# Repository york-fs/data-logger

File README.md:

# Data Logging Board

This is a custom PCB data-logger designed to work on our Formula Student car. It captures data from the vehicle's CAN bus, transmits telemetry, and logs to an SD card. Additionally, the data logger stores configuration information on EEPROM. 

## Key Features
- **CAN bus interface** for vehicle data logging  
- **SD card slot** for onboard storage
- **EEPROM** for storing config data
- **Real-time clock (RTC)** with battery backup for accurate timestamps  
- **USB interface** for configuration and file transfer  
- **UART output** to a SiK telemetry radio for live data streaming  
- **Status LEDs** for logging, USB power, and telemetry status

## PCB Notes
- Designed in KiCad 9.0
- 3D models stored in external library (lib)

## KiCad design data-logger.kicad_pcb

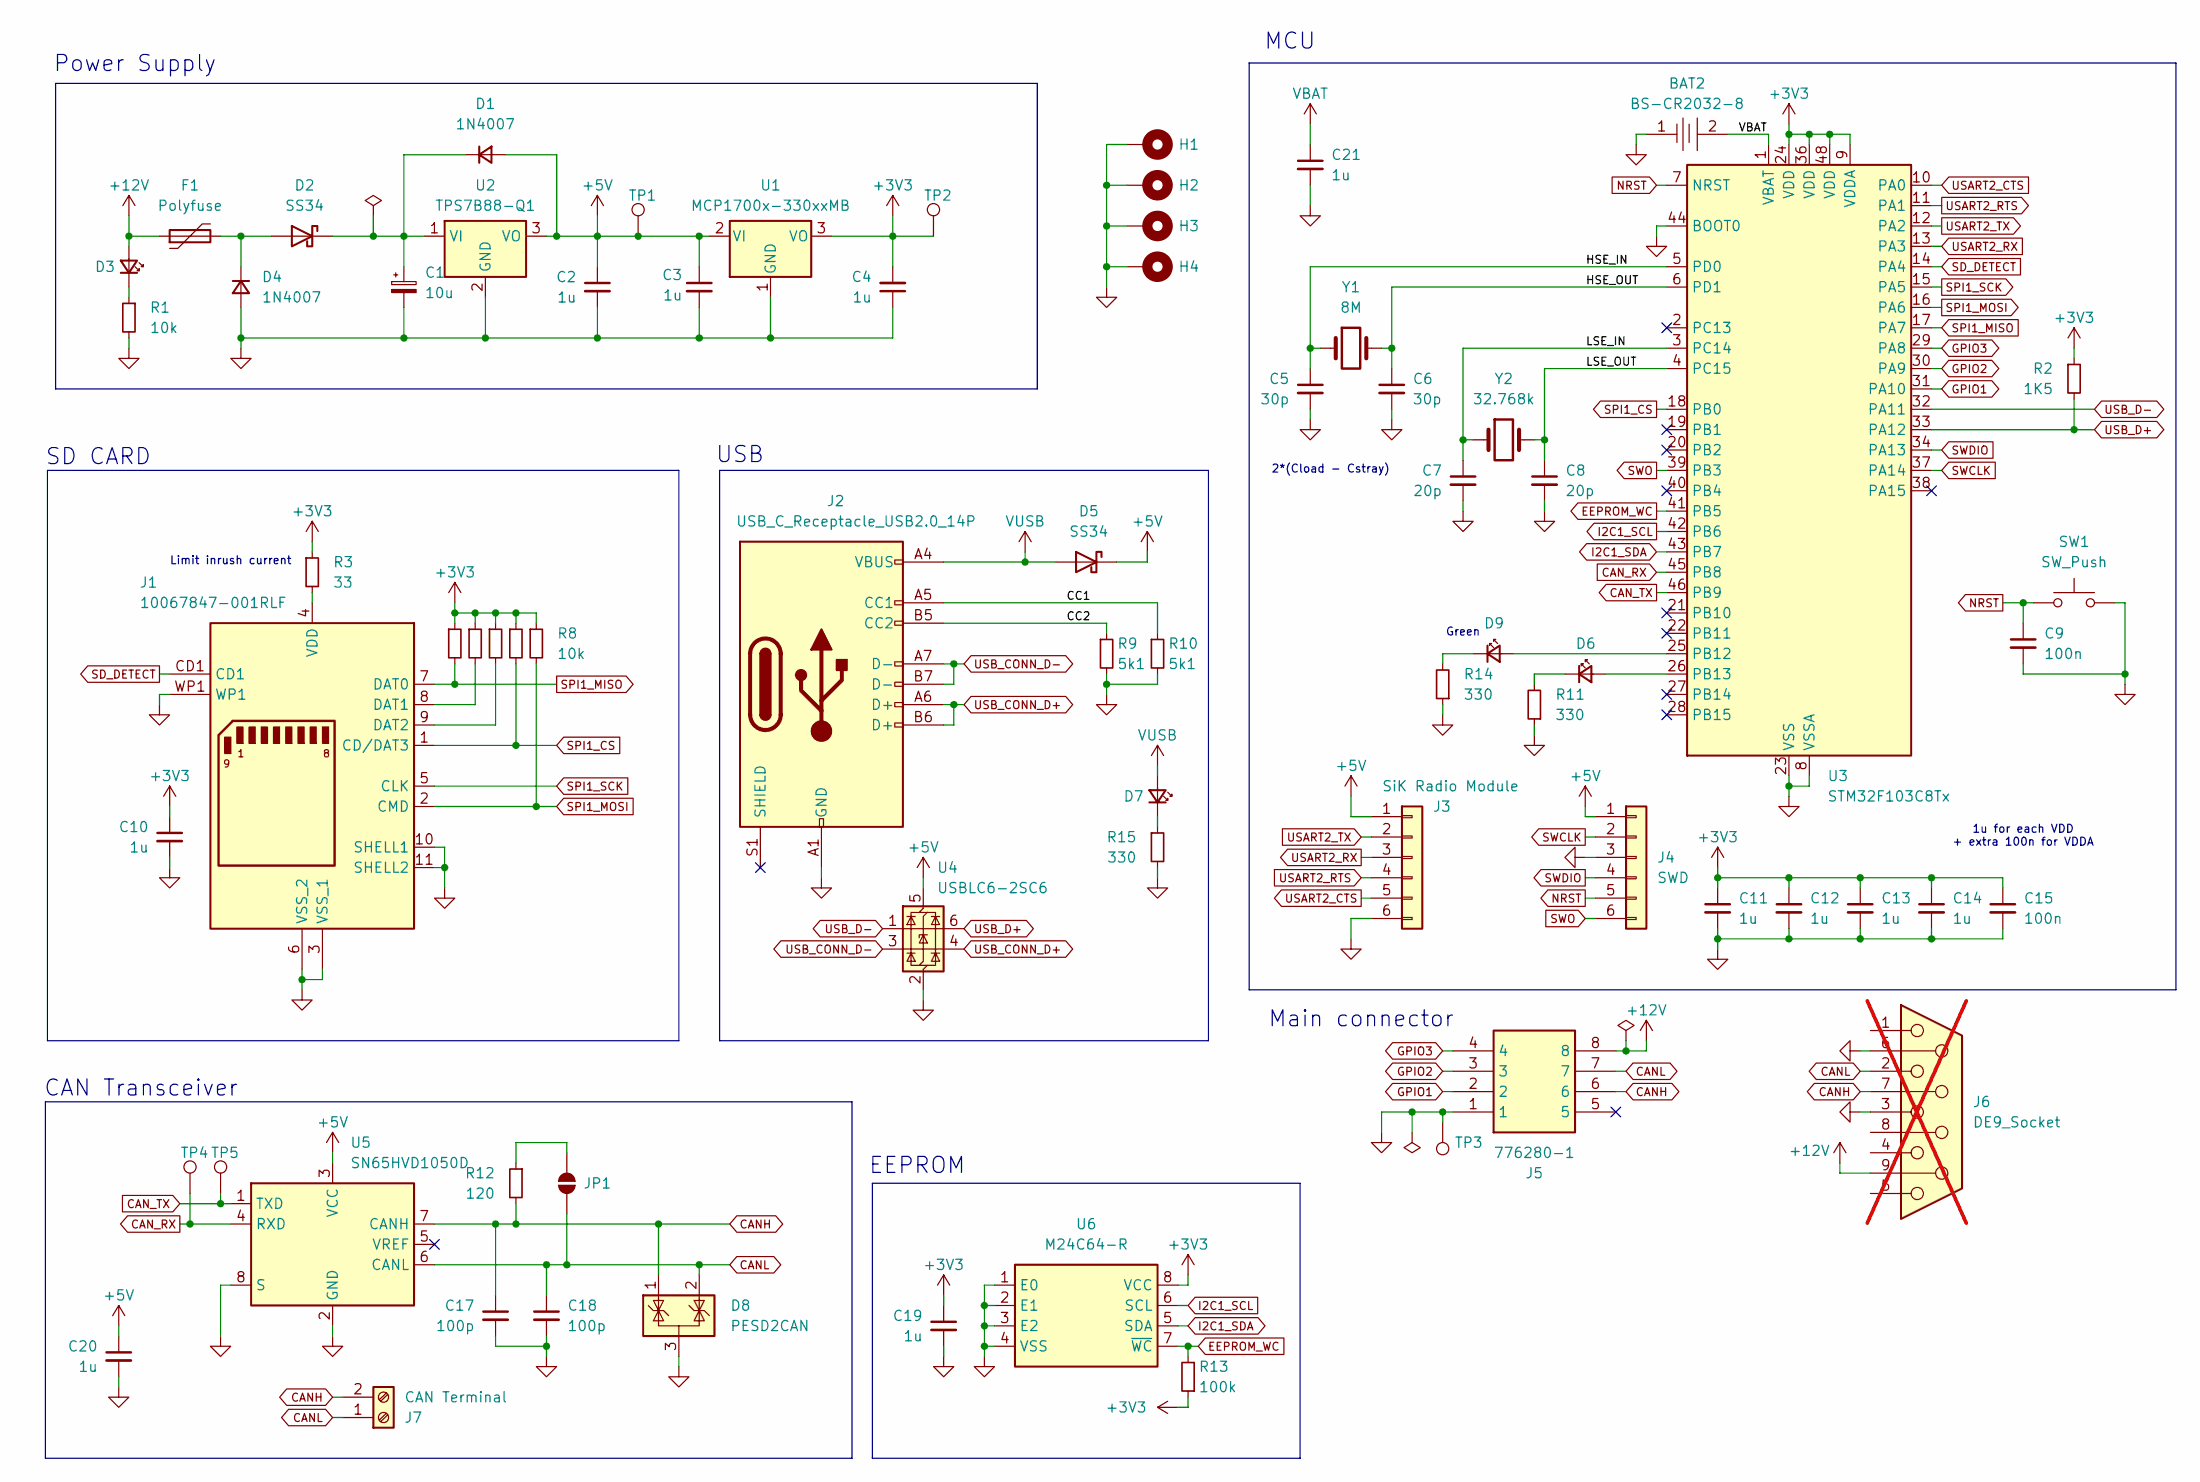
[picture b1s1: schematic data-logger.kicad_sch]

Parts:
BAT2: BS-CR2032-8; BAT-SMD_BS-CR2032-8; LCSC Part C7498149
C1: 10u; CP_Elec_6.3x5.4
C2, C3, C4, C10, C11, C12, C13, C14, C19, C20, C21: 1u; C_0603_1608Metric
C5, C6: 30p; C_0603_1608Metric
C7, C8: 20p; C_0603_1608Metric
C9, C15: 100n; C_0603_1608Metric
C17, C18: 100p; C_0603_1608Metric
D1, D4: 1N4007; D_SOD-123F
D2, D5: SS34; D_SMA
D3, D6, D7, D9: LED_Small; LED_0603_1608Metric
D8: PESD2CAN; SOT-23
F1: Polyfuse; R_0805_2012Metric
H1, H2, H3, H4: MountingHole_Pad; MountingHole_3.2mm_M3_Pad_Via
J1: 10067847-001RLF; 10067847-001RLF_AMP; Mouser Part Number 649-10067847-001RLF
J2: USB_C_Receptacle_USB2.0_14P; USB_C_Receptacle_G-Switch_GT-USB-7010ASV
J3: SiK Radio Module; JST_PH_B6B-PH-K_1x06_P2.00mm_Vertical
J4: SWD; PinHeader_1x06_P2.54mm_Vertical
J5: 776280-1; Mouser Part Number 571-776280-1
J6: DE9_Socket; not fitted
J7: CAN Terminal; TerminalBlock_bornier-2_P5.08mm
JP1: SolderJumper_2_Open; SolderJumper-2_P1.3mm_Open_RoundedPad1.0x1.5mm
R1, R8: 10k; R_0603_1608Metric
R2: 1K5; R_0603_1608Metric
R3, R4, R5, R6, R7: 33; R_0603_1608Metric
R9, R10: 5k1; R_0603_1608Metric
R11, R14, R15: 330; R_0603_1608Metric
R12: 120; R_0603_1608Metric
R13: 100k; R_0603_1608Metric
SW1: SW_Push; SW_Push_SPST_NO_Alps_SKRK
TP1, TP2, TP3, TP4, TP5: TestPoint; TestPoint_Keystone_5000-5004_Miniature
U1: MCP1700x-330xxMB; SOT-89-3
U2: TPS7B88-Q1; TO-252-2
U3: STM32F103C8Tx; LQFP-48_7x7mm_P0.5mm
U4: USBLC6-2SC6; SOT-23-6
U5: SN65HVD1050D; SOIC-8_3.9x4.9mm_P1.27mm
U6: M24C64-R; SOIC-8_3.9x4.9mm_P1.27mm
Y1: 8M; Crystal_SMD_5032-2Pin_5.0x3.2mm
Y2: 32.768k; Crystal_SMD_G8-2Pin_3.2x1.5mm

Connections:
+3V3: C4.2, C10.1, C11.1, C12.1, C13.1, C14.1, C15.1, C19.1, R2.1, R3.1, R4.1, R5.1, R6.1, R7.1, R8.1, R13.1, TP2.1, U1.3 (VO), U3.9 (VDDA), U3.24 (VDD), U3.36 (VDD), U3.48 (VDD), U6.8 (VCC)
+5V: C2.1, C3.1, C20.1, D1.2 (A), D5.1 (K), J3.1, J4.1, TP1.1, U1.2 (VI), U2.3 (VO), U4.5 (VBUS), U5.3 (VCC)
+12V: D3.2 (A), F1.1, J5.8, J6.9
/CC1: J2.A5 (CC1), R10.1
/CC2: J2.B5 (CC2), R9.1
/HSE_IN: C5.1, U3.5 (PD0), Y1.1
/HSE_OUT: C6.1, U3.6 (PD1), Y1.2
/LSE_IN: C7.1, U3.3 (PC14), Y2.1
/LSE_OUT: C8.1, U3.4 (PC15), Y2.2
CANH: C17.1, D8.1 (K), J5.6, J6.7, J7.2, R12.2, U5.7 (CANH)
CANL: C18.1, D8.2 (K), J5.7, J6.2, J7.1, JP1.2 (B), U5.6 (CANL)
CAN_RX: TP4.1, U3.45 (PB8), U5.4 (RXD)
CAN_TX: TP5.1, U3.46 (PB9), U5.1 (TXD)
EEPROM_WC: R13.2, U3.41 (PB5), U6.7 (~WC)
GND: BAT2.1, C1.2, C2.2, C3.2, C4.1, C5.2, C6.2, C7.2, C8.2, C9.2, C10.2, C11.2, C12.2, C13.2, C14.2, C15.2, C17.2, C18.2, C19.2, C20.2, C21.2, D4.2 (A), D8.3 (A), H1.1, H2.1, H3.1, H4.1, J1.3 (VSS_1), J1.6 (VSS_2), J1.10 (SHELL1), J1.11 (SHELL2), J1.WP1, J2.A1 (GND), J2.A12 (GND), J2.B1 (GND), J2.B12 (GND), J3.6, J4.3, J5.1, J6.3, J6.6, R1.2, R9.2, R10.2, R11.1, R14.1, R15.2, SW1.2, TP3.1, U1.1 (GND), U2.2 (GND), U3.8 (VSSA), U3.23 (VSS), U3.35 (VSS), U3.44 (BOOT0), U3.47 (VSS), U4.2 (GND), U5.2 (GND), U5.8 (S), U6.1 (E0), U6.2 (E1), U6.3 (E2), U6.4 (VSS)
GPIO1: J5.2, U3.31 (PA10)
GPIO2: J5.3, U3.30 (PA9)
GPIO3: J5.4, U3.29 (PA8)
I2C1_SCL: U3.42 (PB6), U6.6 (SCL)
I2C1_SDA: U3.43 (PB7), U6.5 (SDA)
NRST: C9.1, J4.5, SW1.1, U3.7 (NRST)
unnamed: C1.1, D1.1 (K), D2.1 (K), U2.1 (VI)
unnamed: D2.2 (A), D4.1 (K), F1.2
unnamed: D3.1 (K), R1.1
unnamed: D6.2 (A), U3.26 (PB13)
unnamed: D6.1 (K), R11.2
unnamed: D7.1 (K), R15.1
unnamed: D9.2 (A), U3.25 (PB12)
unnamed: D9.1 (K), R14.2
unnamed: J1.8 (DAT1), R5.2
unnamed: J1.9 (DAT2), R6.2
unnamed: J1.4 (VDD), R3.2
unnamed: JP1.1 (A), R12.1
SD_DETECT: J1.CD1, U3.14 (PA4)
SPI1_CS: J1.1 (CD/DAT3), R7.2, U3.18 (PB0)
SPI1_MISO: J1.7 (DAT0), R4.2, U3.17 (PA7)
SPI1_MOSI: J1.2 (CMD), R8.2, U3.16 (PA6)
SPI1_SCK: J1.5 (CLK), U3.15 (PA5)
SWCLK: J4.2, U3.37 (PA14)
SWDIO: J4.4, U3.34 (PA13)
SWO: J4.6, U3.39 (PB3)
USART2_CTS: J3.5, U3.10 (PA0)
USART2_RTS: J3.4, U3.11 (PA1)
USART2_RX: J3.3, U3.13 (PA3)
USART2_TX: J3.2, U3.12 (PA2)
USB_CONN_D+: J2.A6 (D+), J2.B6 (D+), U4.4 (I/O2)
USB_CONN_D-: J2.A7 (D-), J2.B7 (D-), U4.3 (I/O2)
USB_D+: R2.2, U3.33 (PA12), U4.6 (I/O1)
USB_D-: U3.32 (PA11), U4.1 (I/O1)
VBAT: BAT2.2, C21.1, U3.1 (VBAT)
VUSB: D5.2 (A), D7.2 (A), J2.A4 (VBUS), J2.A9 (VBUS), J2.B4 (VBUS), J2.B9 (VBUS)

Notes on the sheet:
SD CARD
Main connector
1u for each VDD + extra 100n for VDDA
CAN Transceiver
2*(Cload - Cstray)
MCU
USB
EEPROM
Limit inrush current
Green
Power Supply

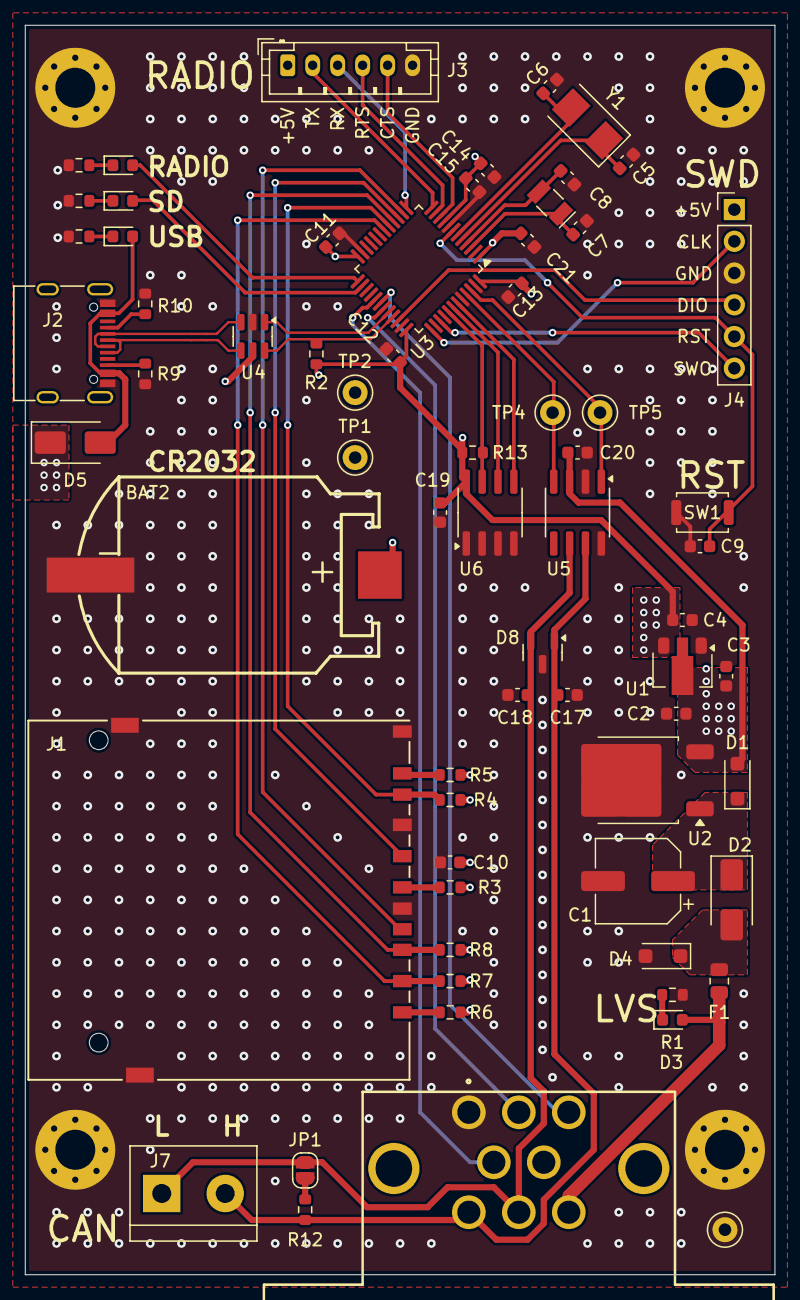
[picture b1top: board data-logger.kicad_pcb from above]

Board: 4 copper layers, 60.0 x 100.0 mm, 71 parts (0 on the bottom side), 51 nets.

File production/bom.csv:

Designator,Footprint,Quantity,Value,LCSC Part #
BAT2,BAT-SMD_BS-CR2032-8,1,BS-CR2032-8,C7498149
C1,CP_Elec_6.3x5.4,1,10u,
"C10, C11, C12, C13, C14, C19, C2, C20, C21, C3, C4",0603,11,1u,
"C15, C9",0603,2,100n,
"C17, C18",0603,2,100p,
"C5, C6",0603,2,30p,
"C7, C8",0603,2,20p,
"D1, D4",D_SOD-123F,2,1N4007,
"D2, D5",D_SMA,2,SS34,
"D3, D6, D7, D9",0603,4,LED_Small,
D8,SOT-23,1,PESD2CAN,
F1,0805,1,Polyfuse,
"H1, H2, H3, H4",MountingHole_3.2mm_M3_Pad_Via,4,MountingHole_Pad,
J1,10067847-001RLF_AMP,1,10067847-001RLF,
J2,USB_C_Receptacle_G-Switch_GT-USB-7010ASV,1,USB_C_Receptacle_USB2.0_14P,
J3,JST_PH_B6B-PH-K_1x06_P2.00mm_Vertical,1,SiK Radio Module,
J4,PinHeader_1x06_P2.54mm_Vertical,1,SWD,
J5,776280-1,1,776280-1,
J7,TerminalBlock_bornier-2_P5.08mm,1,CAN Terminal,
"R1, R8",0603,2,10k,
"R10, R9",0603,2,5k1,
"R11, R14, R15",0603,3,330,
R12,0603,1,120,
R13,0603,1,100k,
R2,0603,1,1K5,
"R3, R4, R5, R6, R7",0603,5,33,
SW1,SW_Push_SPST_NO_Alps_SKRK,1,SW_Push,
"TP1, TP2, TP3, TP4, TP5",TestPoint_Keystone_5000-5004_Miniature,5,TestPoint,
U1,SOT-89-3,1,MCP1700x-330xxMB,
U2,TO-252-2,1,TPS7B88-Q1,
U3,LQFP-48_7x7mm_P0.5mm,1,STM32F103C8Tx,
U4,SOT-23-6,1,USBLC6-2SC6,
U5,SOIC-8_3.9x4.9mm_P1.27mm,1,SN65HVD1050D,
U6,SOIC-8_3.9x4.9mm_P1.27mm,1,M24C64-R,
Y1,Crystal_SMD_5032-2Pin_5.0x3.2mm,1,8M,
Y2,Crystal_SMD_G8-2Pin_3.2x1.5mm,1,32.768k,

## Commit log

2025-09-23 Revision A
2025-09-23 Rev A production files
2025-09-23 Component library for 3D models
2025-09-23 Update README.md
    Fixed formatting
2025-09-23 Update README.md
    Added Render
2025-10-22 Add CI workflow configuration
2025-10-22 Add workflow_dispatch trigger to CI workflow
2025-10-22 kicad-library: Add submodule
2025-11-22 meta: Add gitignore
2025-11-22 meta: Set LF line endings explicitly
2025-11-23 ci: Update to latest kicad workflow
2025-11-23 meta: Add some badges to the README
